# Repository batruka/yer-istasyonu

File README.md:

# Yer İstasyonu

LoRa yer istasyonu kartı: bilgisayara USB ile bağlanır, COM port olarak görünür ve
E220-900T30S modülü üzerinden 868 MHz LoRa ile haberleşir.

```
USB  ->  USB-UART dönüştürücü  ->  E220-900T30S (LoRa, 30 dBm)  ->  SMA anten
```

## Kartlar

| Klasör | USB-UART | Durum |
|---|---|---|
| [`cp2102n/`](cp2102n/) | CP2102N (QFN-24) | **Güncel model.** Tasarım bitti; AUX paket LED'i (D2) eklendi |
| [`ch340g/`](ch340g/) | CH340G (SOIC-16) | Çalışma devam ediyor |

Güncel modelde iki LED var: D1 güç göstergesi, D2 paket göstergesi. D2, E220'nin AUX
pinine bağlı; modül paket gönderirken ya da alırken yanar.

Her klasörde KiCad 10 projesi (`.kicad_pro`, `.kicad_sch`, `.kicad_pcb`) ve `uretim/`
klasörü var. CP2102N'de Gerber, PDF ve alışveriş listesi; CH340G'de şimdilik sadece şema PDF'i.

## Açmak için

KiCad 10 ile `.kicad_pro` dosyasını açın. Şema ve PCB, kullandıkları sembol ve ayak
izlerini kendi içinde taşır; ek kütüphane kurmadan açılır.

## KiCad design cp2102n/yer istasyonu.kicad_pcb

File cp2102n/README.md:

# Yer İstasyonu — CP2102N sürümü

```
USB-C  ->  CP2102N (USB-UART)  ->  E220-900T30S (LoRa, 30 dBm)  ->  SMA anten
```

## Kart

- 2 katman FR4, 1.6 mm, 34 x 90 mm
- Bütün parçalar üst yüzde
- Pasifler 0805 (lehimleme için geniş pedli)

## Ana parçalar

| Ref | Parça | Not |
|---|---|---|
| U3 | CP2102N-A02-GQFN24R | USB-UART, kendi 3.3V regülatörüyle beslenir |
| U2 | E220-900T30S | LoRa modülü, VBUS'tan (5V) beslenir |
| U1 | AMS1117-3.3 | 3.3V çıkışı sadece J1 başlığına gider |
| U4 | SRV05-4 | USB veri hatları için ESD koruma |
| J3 | HRO TYPE-C-31-M-12 | USB-C; CC hatlarında 5.1k (R2, R3) |
| J4 | BWSMA-KWE-Z001 | Dik açılı SMA |
| J2, J5 | Pin başlığı | M0 / M1 seçimi (jumper takılı = 0) |
| D1 | Yeşil LED | Güç göstergesi |
| D2 | Yeşil LED | Paket göstergesi: VBUS → R12 (1k) → D2 → E220 AUX; AUX LOW (meşgul) iken yanar |

## Anten hattı

E220'den SMA'ya 6.9 mm'lik eş düzlemli hat (GCPW): yol 2.0 mm, iki yanda 0.5 mm boşluk,
altta dolu GND. 1.6 mm FR4 (εr ≈ 4.5) için yaklaşık 50 Ω.

## Dosyalar

| Dosya | İçerik |
|---|---|
| `yer istasyonu.kicad_pro / _sch / _pcb` | KiCad 10 projesi |
| `uretim/gerber.zip` | Gerber + delik dosyaları |
| `uretim/sema.pdf` | Devre şeması |
| `uretim/pcb.pdf` | PCB üst yüz (sayfa 1) ve alt yüz (sayfa 2, aynalı) |
| `uretim/alisveris_listesi.xlsx` | Özdisan + LCSC parça listesi (25.10.2026 stok/fiyat) |

## Kullanım

- Anten takılı değilken karta güç vermeyin.
- J2 ve J5 jumper takılı: M0 = M1 = 0, normal çalışma. M0 = M1 = 1 ayar modudur.
- E220 gönderim anında ~610 mA çeker. En az 1 A verebilen bir USB port ya da adaptör kullanın.
- Seri port: Silicon Labs CP210x sürücüsü, 9600 baud 8N1 (E220 fabrika ayarı).
- D2 her paket gönderiminde ve alımında kısa süre yanar. Karta güç verilince de E220'nin
  açılış kontrolü sırasında bir kez yanıp söner.
- D2 yerine kırmızı/sarı LED takmayın: Vf ~2 V olan LED, AUX HIGH iken de hafif yanar ve
  AUX pinine akım gönderir. Bu devre Vf'si 2.7–3.4 V olan yeşil LED'e göre hesaplandı.

## Bilinen durumlar

- DRC (KiCad 10.0.8, D2/R12 dahil): eksik bağlantı ve boşluk hatası yok. E220'nin 9. pini
  (GND) döküme tek kolla bağlı; çalışmayı etkilemez.
- Baskı (silkscreen) uyarıları: C12 ile C13'ün etiketleri üst üste biniyor, D2 etiketi
  kendi çerçevesine değiyor. Sadece görünüş; elektriksel etkisi yok.
- C5 (10 µF) ve C6 (100 nF) şemada var, PCB'de yok.
- `3d_ust.png`: USB-C (J3) ve SMA (J4) için KiCad kütüphanesinde 3D model olmadığından bu
  ikisi gövdesiz görünür.
- Asitle üretimde vialar kaplamasızdır: her viaya tel geçirip iki yüzden lehimleyin
  (vialar 0.6 / 0.3 mm).

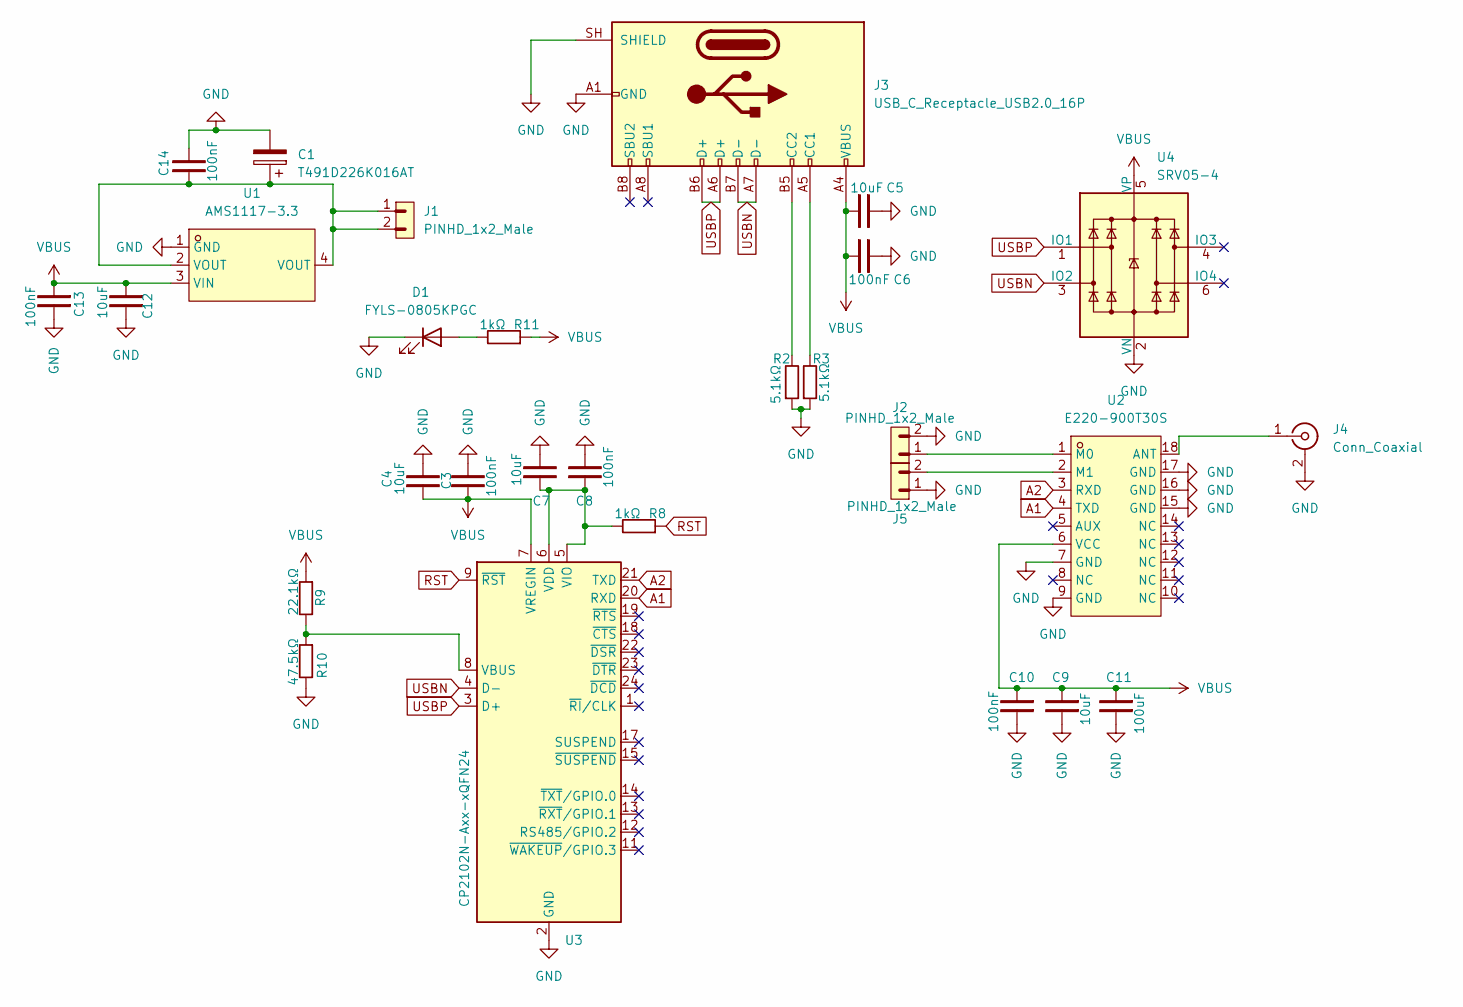
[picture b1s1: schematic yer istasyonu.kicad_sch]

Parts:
C1: T491D226K016AT; CP_EIA-7343-31_Kemet-D; LCSC Part C1952964
C3, C6, C8, C10, C13, C14: 100nF; C_0805_2012Metric_Pad1.18x1.45mm_HandSolder
C4, C5, C7, C9, C12: 10uF; C_0805_2012Metric_Pad1.18x1.45mm_HandSolder
C11: 100uF; CP_Elec_6.3x5.4
D1: FYLS-0805KPGC; LED_0805_2012Metric_Pad1.15x1.40mm_HandSolder
J1, J2, J5: PINHD_1x2_Male; PinHeader_1x02_P2.54mm_Vertical
J3: USB_C_Receptacle_USB2.0_16P; USB_C_Receptacle_HRO_TYPE-C-31-M-12
J4: Conn_Coaxial; SMA_BAT_Wireless_BWSMA-KWE-Z001
R2, R3: 5.1kΩ; R_0805_2012Metric_Pad1.20x1.40mm_HandSolder
R8, R11: 1kΩ; R_0805_2012Metric_Pad1.20x1.40mm_HandSolder
R9: 22.1kΩ; R_0805_2012Metric_Pad1.20x1.40mm_HandSolder
R10: 47.5kΩ; R_0805_2012Metric_Pad1.20x1.40mm_HandSolder
U1: AMS1117-3.3; SOT-223-3_L6.5-W3.4-P2.30-LS7.0-BR; MPN AMS1117-3.3; LCSC Part C6186
U2: E220-900T30S; WIRELM-SMD_E220-900T30S; MPN E220-900T30S; LCSC Part C970286
U3: CP2102N-Axx-xQFN24; QFN-24-1EP_4x4mm_P0.5mm_EP2.6x2.6mm
U4: SRV05-4; SOT-23-6

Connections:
A1: U2.4 (TXD), U3.20 (RXD)
A2: U2.3 (RXD), U3.21 (TXD)
AUX: U2.5 (AUX); also elsewhere on the board
GND: C1.2, C3.2, C4.2, C5.2, C6.2, C7.2, C8.2, C9.2, C10.2, C11.2, C12.2, C13.2, C14.2, D1.1 (K), J2.2, J3.A1 (GND), J3.A12 (GND), J3.B1 (GND), J3.B12 (GND), J3.SH (SHIELD), J4.2 (Ext), J5.1, R2.1, R3.1, R10.2, U1.1 (GND), U2.7 (GND), U2.9 (GND), U2.15 (GND), U2.16 (GND), U2.17 (GND), U3.2 (GND), U3.25 (GND), U4.2 (VN)
unnamed: C1.1, C14.1, J1.1, J1.2, U1.2 (VOUT), U1.4 (VOUT)
unnamed: D1.2 (A), R11.2
unnamed: J3.A5 (CC1), R3.2
unnamed: J3.B5 (CC2), R2.2
unnamed: J4.1 (In), U2.18 (ANT)
unnamed: J2.1, U2.1 (M0)
unnamed: J5.2, U2.2 (M1)
unnamed: R9.2, R10.1, U3.8 (VBUS)
unnamed: C7.1, C8.1, R8.2, U3.5 (VIO), U3.6 (VDD)
RST: R8.1, U3.9 (~RST)
USBN: J3.A7 (D-), J3.B7 (D-), U3.4 (D-), U4.3 (IO2)
USBP: J3.A6 (D+), J3.B6 (D+), U3.3 (D+), U4.1 (IO1)
VBUS: C3.1, C4.1, C5.1, C6.1, C9.1, C10.1, C11.1, C12.1, C13.1, J3.A4 (VBUS), J3.A9 (VBUS), J3.B4 (VBUS), J3.B9 (VBUS), R9.1, R11.1, U1.3 (VIN), U2.6 (VCC), U3.7 (VREGIN), U4.5 (VP); also elsewhere on the board

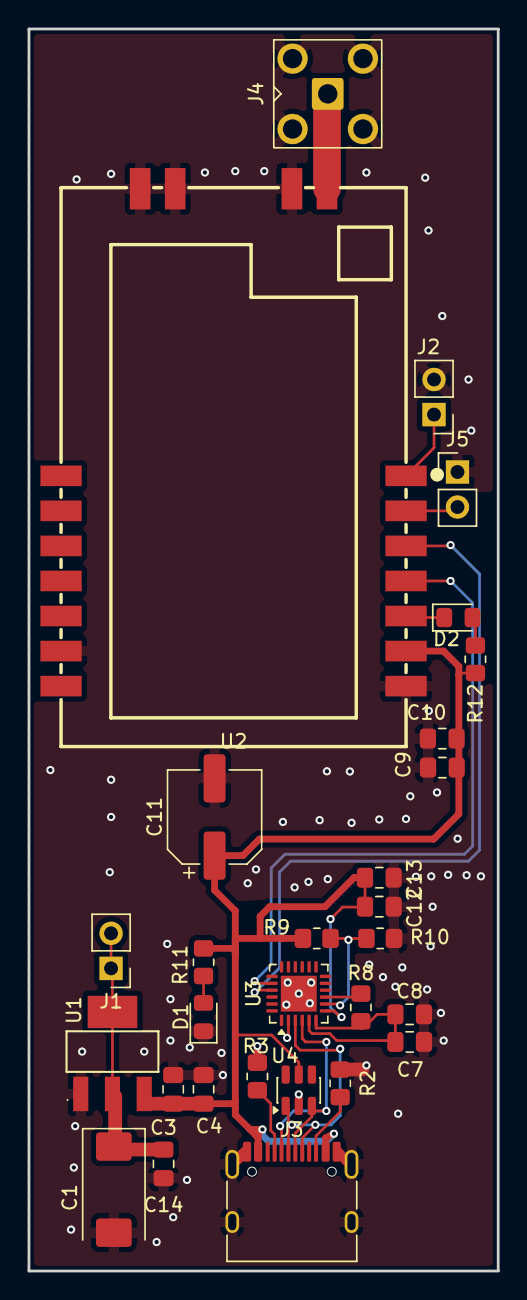
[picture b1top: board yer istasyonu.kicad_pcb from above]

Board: 2 copper layers, 34.0 x 90.0 mm, 29 parts (0 on the bottom side), 18 nets.

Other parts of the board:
D2: FYLS-0805KPGC; LED_0805_2012Metric_Pad1.15x1.40mm_HandSolder
R12: 1kΩ; R_0805_2012Metric_Pad1.20x1.40mm_HandSolder

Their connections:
AUX: D2.1 (K); also elsewhere on the board
unnamed: D2.2 (A), R12.1
VBUS: R12.2; also elsewhere on the board

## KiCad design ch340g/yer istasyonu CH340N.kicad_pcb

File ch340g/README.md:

# Yer İstasyonu — CH340G sürümü

> **Çalışma devam ediyor.** PCB yerleşimi ve yolları bitmedi; bu klasörden üretim yapmayın.

```
USB-C (Pololu breakout)  ->  CH340G (USB-UART)  ->  E220-900T30S (LoRa, 30 dBm)  ->  SMA anten
```

CP2102N sürümünden farkı: takım kuralına uymak için SOP'tan küçük kılıf kullanılmadı.
QFN CP2102N yerine SOIC-16 CH340G, çıplak USB-C yerine Pololu breakout, SOT-23-6 ESD
yerine SOT-23 ESD var.

## Ana parçalar

| Ref | Parça | Not |
|---|---|---|
| U3 | CH340G | USB-UART, SOIC-16; +3V3 ile beslenir (VCC = V3) |
| Y1, C15, C16 | 12 MHz kristal + 2 x 22 pF | CH340G saat kaynağı |
| U2 | E220-900T30S | LoRa modülü, VBUS'tan (5V) beslenir |
| U1 | AMS1117-3.3 | +3V3: CH340G ve J1 başlığı |
| U4 | PJDLC05 | USB D+/D− ESD koruma (SOT-23) |
| J3 | Pololu USB 2.0 Type-C breakout (usb07b) | CC 5.11k dirençleri breakout üzerinde |
| J4 | BWSMA-KWE-Z001 | Dik açılı SMA |
| J2, J5 | Pin başlığı | M0 / M1 seçimi |

Dosya adları tarihsel sebeple `yer istasyonu CH340N.*`; kartta CH340G kullanılıyor.

## Tasarım kuralları (projede ayarlı)

- Sinyal yolu 0.3 mm, boşluk 0.25 mm
- VBUS ve GND ("Guc" sınıfı) 1.2 mm
- Via 2.6 / 1.6 mm (1 mm perçin için)
- J1/J2/J5 ve J3 ayak izleri perçinli: delik 1.6 mm, ped 2.25 mm

## Yapılacaklar

- [ ] Kart sınırı (Edge.Cuts)
- [ ] Anten yolu (E220 pin 18 → J4)
- [ ] Şema ile PCB'yi eşitle (F8): C12, C13, C14 PCB'de yok; PCB'deki C5, C6 şemada yok
- [ ] ERC: bir güç ağı sürülmüyor (#PWR013), PWR_FLAG gerekebilir
- [ ] DRC temizliği, ardından Gerber / PDF

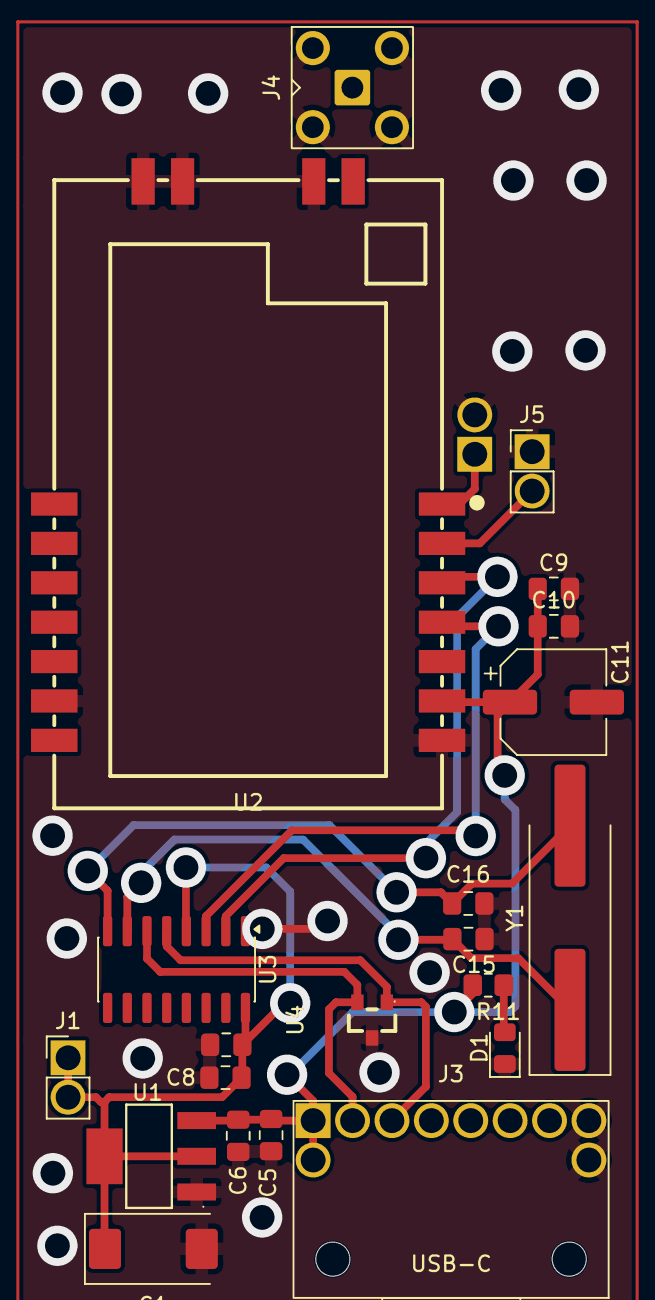
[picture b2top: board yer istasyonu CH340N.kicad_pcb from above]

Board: 2 copper layers, 22 parts (1 on the bottom side), 13 nets.

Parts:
C1: T491D226K016AT; CP_EIA-7343-31_Kemet-D
C5, C9, C17: 10uF; C_0805_2012Metric_Pad1.18x1.45mm_HandSolder
C6, C8, C10: 100nF; C_0805_2012Metric_Pad1.18x1.45mm_HandSolder
C11: 100uF; CP_Elec_6.3x5.4
C15, C16: 22pF; C_0805_2012Metric_Pad1.18x1.45mm_HandSolder
D1: FYLS-0805KPGC; LED_0805_2012Metric_Pad1.15x1.40mm_HandSolder
J1, J2, J5: PINHD_1x2_Male; PinHeader_1x02_P2.54mm_Voltera
J3: Pololu USB-C (usb07b); Pololu_USB07B_Voltera
J4: Conn_Coaxial; SMA_BAT_Wireless_BWSMA-KWE-Z001
R11: 1kΩ; R_0805_2012Metric_Pad1.20x1.40mm_HandSolder
U1: AMS1117-3.3; SOT-223-3_L6.5-W3.4-P2.30-LS7.0-BR
U2: E220-900T30S; WIRELM-SMD_E220-900T30S
U3: CH340G; SOIC-16_3.9x9.9mm_P1.27mm
U4: PJDLC05; SOT-23_L2.9-W1.3-P1.90-LS2.4-BR
Y1: 12MHz; Crystal_SMD_HC49-SD_HandSoldering

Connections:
+3V3: C1.1, C8.1, C17.1, J1.1, J1.2, U1.2 (VOUT), U1.4 (VOUT), U3.4 (V3), U3.16 (VCC)
A1: U2.4 (TXD), U3.3 (RXD)
A2: U2.3 (RXD), U3.2 (TXD)
GND: C1.2, C5.2, C6.2, C8.2, C9.2, C10.2, C11.2, C15.2, C16.2, C17.2, D1.1 (K), J2.2, J3.8 (GND), J3.10 (GND), J4.2 (Ext), J5.1, U1.1 (GND), U2.7 (GND), U2.9 (GND), U2.15 (GND), U2.16 (GND), U2.17 (GND), U3.1 (GND), U4.3
unnamed: D1.2 (A), R11.2
unnamed: J4.1 (In), U2.18 (ANT)
unnamed: J2.1, U2.1 (M0)
unnamed: J5.2, U2.2 (M1)
unnamed: C15.1, U3.7 (XI), Y1.1
unnamed: C16.1, U3.8 (XO), Y1.2
USBN: J3.2 (D-), U3.6 (UD-), U4.2
USBP: J3.3 (D+), U3.5 (UD+), U4.1
VBUS: C5.1, C6.1, C9.1, C10.1, C11.1, J3.1 (VBUS), J3.9 (VBUS), R11.1, U1.3 (VIN), U2.6 (VCC)
